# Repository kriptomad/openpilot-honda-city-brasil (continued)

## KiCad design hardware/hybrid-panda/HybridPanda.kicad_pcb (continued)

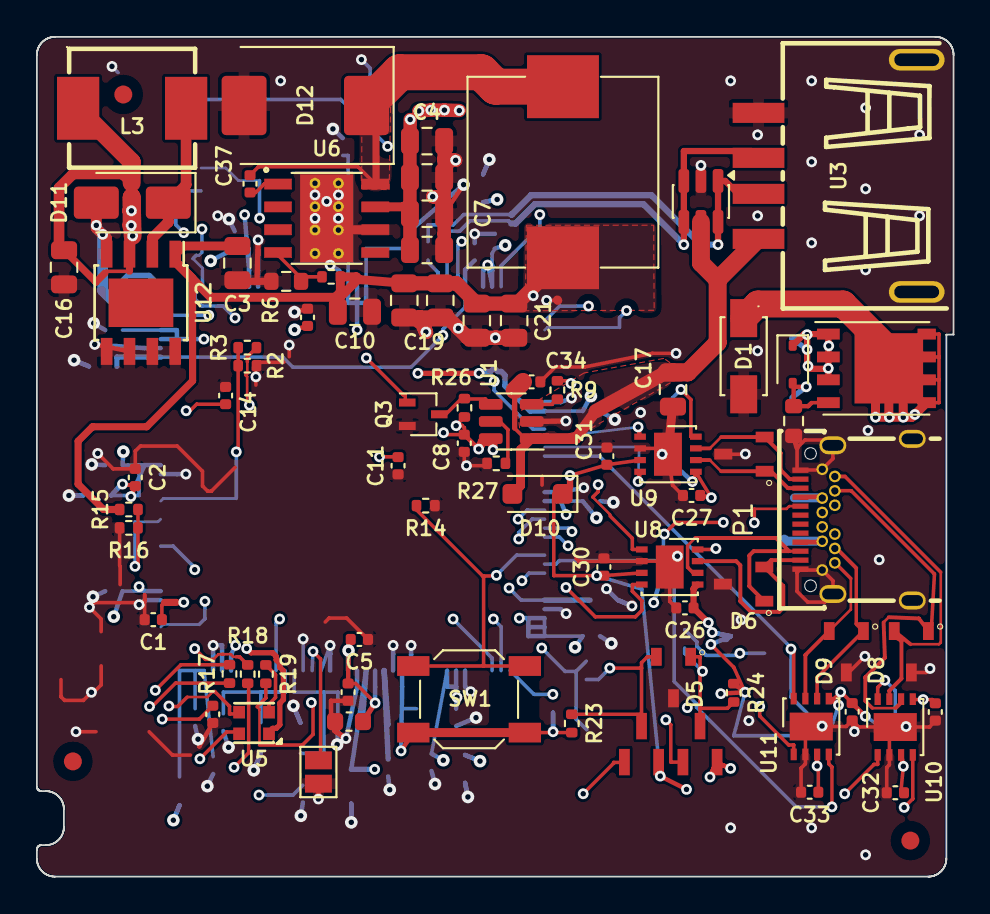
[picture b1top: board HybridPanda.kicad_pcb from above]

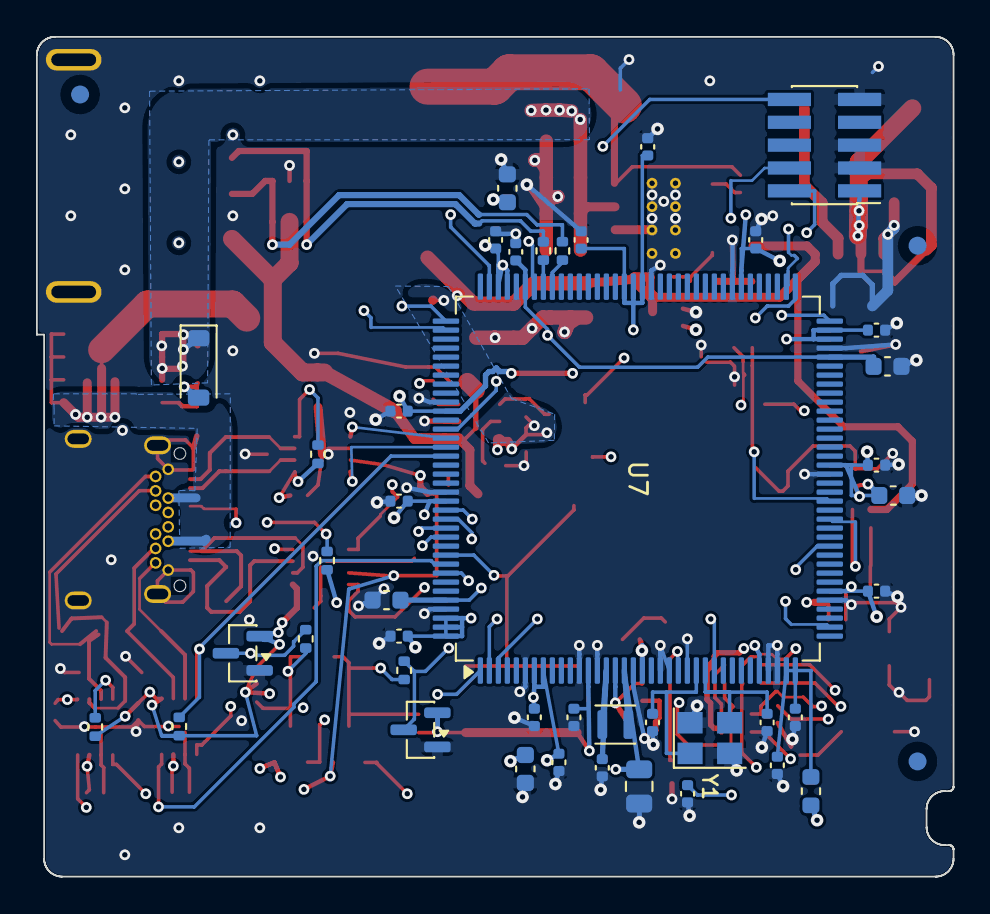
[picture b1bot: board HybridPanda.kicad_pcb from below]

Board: 4 copper layers, 50.9 x 46.7 mm, 125 parts (45 on the bottom side), 63 nets.

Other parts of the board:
FID1, FID2, FID3, FID4, FID5, FID6: Fiducial; Fiducial_1mm_Mask2mm

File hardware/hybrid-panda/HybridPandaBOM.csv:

"Id";"Designator";"Footprint";"Quantity";"Designation";"Supplier and ref";
1;"C1, C2, C5, C11, C14, C26, C27, C28, C29, C30, C31, C32, C33";"C_0402_1005Metric";13;"100NF";;;
2;"C3, C10, C16, C17, C18, C19, C20, C21";"C_0805_2012Metric";8;"47uF";;;
3;"C4, C12, C42";"C_0805_2012Metric";3;"10uF";;;
4;"C6, C7";"C_0805_2012Metric";2;"2.2uF";;;
5;"C8";"C_0402_1005Metric";1;"10uF";;;
6;"C23, C24";"C_0402_1005Metric";2;"18pF";;;
7;"C34";"C_0402_1005Metric";1;"0.1uF";;;
8;"C37";"C_0402_1005Metric";1;"10nF (LOW ESR)";;;
9;"C38, C44, C45, C46, C47, C48, C49, C50, C51, C52, C53, C54, C55, C56, C57, C58, C59";"C_0402_1005Metric";17;"100nF";;;
10;"C39, C40";"C_0603_1608Metric";2;"2.2uF";;;
11;"C41";"C_0402_1005Metric";1;"220pF";;;
12;"C43, C63";"C_0402_1005Metric";2;"1uF";;;
13;"C60, C61, C62, C65";"C_0603_1608Metric";4;"4.7uF";;;
14;"C64";"C_0402_1005Metric";1;"2.2uF";;;
15;"D1";"DIOM4325X250N";1;"SMAJ16CA-13-F";;;
16;"D2";"D_SOD-323";1;"BAS40WS 43";;;
17;"D5, D6, D7, D8, D9";"SOT95P230X110-3N";5;"PESD2CAN,215";;;
18;"D10";"D_SOD-123F";1;"BAS70H 115";;;
19;"D11";"D_SMA";1;"B320AE-13";;;
20;"D12";"D_SMC";1;"SM540C";;;
21;"D13, D14";"SOT-23";2;"BAT54S";;;
22;"D15";"D_SOD-123";1;"BZT52C12";;;
23;"FB1";"L_0603_1608Metric";1;"600R@100MHz";;;
24;"J1";"PinHeader_2x05_P1.27mm_Vertical_SMD";1;"SWD";;;
25;"L3";"IND-SMD_L7.3-W6.8";1;"47uH 2A - SMMS0650-470M";;;
26;"L4";"L_10.5x11.5_H4.0";1;"15uH";;;
27;"L5";"L_Murata_DFE201610P";1;"2.2uH DFE201610E-2R2M";;;
28;"P1";"USB-C-SMD_TYPE-C-USB-20";1;"TYPE-C-31-M-04";;;
29;"Q1, Q2";"SOT23-3";2;"DDTA143ECA-7-F P08";;;
30;"Q3";"SOT-323_SC-70";1;"PDTC114EU";;;
31;"Q4";"PowerPAK_SO-8_Single";1;"HY12P03C2";;;
32;"R1";"R_0603_1608Metric";1;"10k";;;
33;"R2";"R_0402_1005Metric";1;"1K";;;
34;"R3, R9, R23, R24, R26";"R_0402_1005Metric";5;"10K";;;
35;"R5";"R_0402_1005Metric";1;"10K (1%)";;;
36;"R6";"R_0603_1608Metric";1;"3.16K (1%)";;;
37;"R14, R15, R16, R28, R29, R30, R31, R32, R33";"R_0402_1005Metric";9;"10k";;;
38;"R17";"R_0402_1005Metric";1;"180R";;;
39;"R18";"R_0402_1005Metric";1;"110R";;;
40;"R19";"R_0402_1005Metric";1;"100R";;;
41;"R20, R21";"R_0402_1005Metric";2;"22R";;;
42;"R27";"R_0402_1005Metric";1;"2.4K";;;
43;"SW1";"SW_SPST_SKQG_WithStem";1;"SW_Push";;;
44;"U1";"SOT-23-6";1;"AP22615AWU-7";;;
45;"U3";"USB-A-TH_10.0QHHTZB6.3";1;"10_0_QHHTZB6_3";;;
46;"U5";"LED-ARRAY-SMD_4P-L2.2-W2.1-BR";1;"FM-B1921RGBA-SH";;;
47;"U6";"CONV_TPS5450DDAR";1;"TPS5450DDAR";;;
48;"U7";"LQFP-144_20x20mm_P0.5mm";1;"STM32H725ZGT6";;;
49;"U8, U9, U10, U11";"DFN-8-1EP_3x3mm_P0.65mm_EP1.55x2.4mm";4;"TJA1042TK-3";;;
50;"U12";"Diodes_PSOP-8";1;"XL1509-3.3";;;
51;"U13";"SOT-23-6";1;"USBLC6-2SC6";;;
52;"Y1";"Crystal_SMD_3225-4Pin_3.2x2.5mm";1;"25MHz X322525MOB4SI";;;

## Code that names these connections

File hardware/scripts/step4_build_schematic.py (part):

"""step4_build_schematic.py - STEP 4: rebuild hardware/hybrid-panda/HybridPanda.kicad_sch around the STM32H725ZGT6.

What it does (deterministic, re-runnable from the baseline copy made by step4_copy_and_roundtrip.py):
  1. deletes the F413 block (U7 + HSE/BOOT/VCAP/LED resistors/labels), the 5V-sense divider and the GPS block
  2. renames CANx_* labels to the firmware bus naming (BUS0/BUS1N/BUS1O/BUS2, EN->STB)
  3. enlarges the sheet to A1 and places the H725 (unit 1) with stubs, global labels, power rails and no-connects
  4. adds support blocks: HSE 25 MHz, BOOT0, NRST, SWD header, VCAP, SMPS inductor, VDDA filter, LED resistors,
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# ----------------------------------------------------------------------------- MCU pin plan (port -> net label)
# labels are global labels; shape per KiCad semantics
MCU_LABELS: dict[str, tuple[str, str]] = {
    "PB9": ("BUS0_TX", "bidirectional"), "PB8": ("BUS0_RX", "bidirectional"), "PG11": ("BUS0_STB", "bidirectional"),
    "PB6": ("BUS1N_TX", "bidirectional"), "PB5": ("BUS1N_RX", "bidirectional"), "PB3": ("BUS1N_STB", "bidirectional"),
    "PB13": ("BUS1O_TX", "bidirectional"), "PB12": ("BUS1O_RX", "bidirectional"), "PB4": ("BUS1O_STB", "bidirectional"),
    "PG9": ("BUS2_TX", "bidirectional"), "PG10": ("BUS2_RX", "bidirectional"), "PD7": ("BUS2_STB", "bidirectional"),
    "PA11": ("USB_D-", "bidirectional"), "PA12": ("USB_D+", "bidirectional"),
    "PB14": ("USB_LOAD", "output"),
    "PF11": ("VoltageSens", "input"),
    "PC4": ("SBU1_ADC", "input"), "PA1": ("SBU2_ADC", "input"),
    "PC10": ("relay_SBU1", "output"), "PC11": ("relay_SBU2", "output"),
    "PE4": ("LED_RED", "output"), "PE3": ("LED_GREEN", "output"), "PE2": ("LED_BLUE", "output"),
    "PB1": ("5VOUT_S", "input"),
    "PH0": ("HSE_IN", "passive"), "PH1": ("HSE_OUT", "passive"),
    "PA13": ("SWDIO", "bidirectional"), "PA14": ("SWCLK", "input"),
    # pin-name keys for non-port pins
    "BOOT0": ("BOOT0", "passive"), "NRST": ("NRST", "passive"),
    "VLXSMPS": ("VLXSMPS", "passive"), "VFBSMPS": ("VFBSMPS", "passive"), "VREF+": ("VDDA", "passive"),
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}
MCU_TO_3V3 = {"PDR_ON"}
# hw-type straps: board.h detects with internal pull-up, RED = all four read low -> hard-wired to GND
MCU_TO_GND = {"PF7", "PF8", "PF9", "PF10"}

# deletion regions (x0, x1, y0, y1)
REGIONS = [(258, 382, 228, 326), (238, 258, 255, 282), (105, 200, 265, 350)]
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            bottom.append(ax)
            used[f"{p.name}#{p.number}"] = "GND"
    ytop = MY - 93.98
    # HW_ID straps: join the four stub ends vertically and put one GND above the highest (below is PF11/VoltageSens)
    gnd_pts.sort(key=lambda t: t[1])
    gx = gnd_pts[0][0]
    assert all(x == gx for x, _ in gnd_pts), gnd_pts
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                  datasheet=bom["hse"].get("crystal_ds", "~"))
    pp = b.pins_abs(y1)
    b.wire(*pp["4"], 800.10, 185.42); b.pwr("GND", 800.10, 185.42, 180)
    b.wire(*pp["1"], 792.48, 190.50); b.wire(792.48, 190.50, L, 190.50); b.label("HSE_IN", L, 190.50, 180, "passive")
    b.wire(*pp["3"], 807.72, 190.50); b.wire(807.72, 190.50, 812.80, 190.50); b.label("HSE_OUT", 812.80, 190.50, 0, "passive")
    c23 = b.cap(bom["hse"]["cl_value"], 792.48, 195.58, ref="C23"); c24 = b.cap(bom["hse"]["cl_value"], 807.72, 195.58, ref="C24")
    for c, x in ((c23, 792.48), (c24, 807.72)):
        cp = b.pins_abs(c)
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
    # --- VCAP 2x2.2uF
    b.text("VCAP", 790.0, 286.0)
    b.wire(L, 292.10, 800.10, 292.10); b.label("VCAP", L, 292.10, 180, "passive")
    for x in (792.48, 800.10):
        c = b.cap("2.2uF", x, 297.18, fp="Capacitor_SMD:C_0603_1608Metric"); cp = b.pins_abs(c)
        b.wire(x, 292.10, *cp["1"]); b.wire(*cp["2"], x, 302.26); b.pwr("GND", x, 302.26)
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
    # --- SMPS: VLXSMPS -> L 2.2uH -> VFBSMPS, 220pF at VLX, 10uF at VFB, PWR_FLAG on VLXSMPS
    b.text("SMPS step-down", 790.0, 309.0)
    b.wire(L, 314.96, 795.02, 314.96); b.label("VLXSMPS", L, 314.96, 180, "passive")
    b.wire(795.02, 314.96, 800.10, 314.96); b.junction(795.02, 314.96); b.flag(795.02, 314.96)
    ind = b.symbol("Device", "L", "L", bom["smps"]["l_value"], bom["smps"]["l_fp"], 803.91, 314.96, 90, datasheet=bom["smps"].get("l_ds", "~"))
    lp = b.pins_abs(ind)
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        b.wire(x, 337.82, *cp["1"]); b.junction(x, 337.82); b.wire(*cp["2"], x, 347.98); b.pwr("GND", x, 347.98)

    # --- LED series resistors (reuse R17/R18/R19 values from baseline: 180R blue, 110R green, 100R red)
    b.text("LED drivers (PE4/PE3/PE2, active low)", 790.0, 351.0)
    for y, ref, val, net_in, net_out in ((355.60, "R19", "100R", "LED_RED", "RED-"),
                                          (360.68, "R18", "110R", "LED_GREEN", "GREEN-"),
                                          (365.76, "R17", "180R", "LED_BLUE", "BLUE-")):
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        b.wire(*dp["2"], dp["2"][0], y + 7.62); b.pwr("+3.3V", dp["2"][0], y + 7.62, 180)  # K -> 3V3
        b.wire(*dp["1"], dp["1"][0], y + 7.62); b.pwr("GND", dp["1"][0], y + 7.62, 0)      # A -> GND

    # --- 5VOUT_S divider (R15/R16 10k, +5V -> PB1)
    b.text("5V sense (PB1)", 790.0, 414.0)
    b.pwr("+5V", 792.48, 419.10)
    r15 = b.res("10k", 792.48, 424.18, ref="R15"); rp = b.pins_abs(r15)
    b.wire(792.48, 419.10, *rp["1"]); b.wire(*rp["2"], L, 426.72); b.label("5VOUT_S", L, 426.72, 180, "input")
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
def phase_project():
    """project file: name + ERC pin-conflict map (power_out<->power_out = warning, needed because the KiCad H7 symbol
    declares the three VCAP pins as power_out while ST requires them tied together; D-19)."""
    pro = PROJ / "HybridPanda.kicad_pro"
    d = json.loads(pro.read_text(encoding="utf-8"))
    d["meta"]["filename"] = "HybridPanda.kicad_pro"
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
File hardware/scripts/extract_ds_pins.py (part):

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
# (port pin, firmware source, function required, net name in new schematic)
REQUIRED = [
    ("PA11", "stm32h7/peripherals.h", "OTG_HS_DM AF10 (USB FS PHY interno; DS nomeia OTG_HS)", "USB_DM"),
    ("PA12", "stm32h7/peripherals.h", "OTG_HS_DP AF10", "USB_DP"),
    ("PF11", "stm32h7/peripherals.h", "ADC1_INP2 ADC1 ch2 (VOLT_S)", "VOLT_S"),
    ("PB8",  "stm32h7/peripherals.h", "FDCAN1_RX AF9", "FDCAN1_RX"),
    ("PB9",  "stm32h7/peripherals.h", "FDCAN1_TX AF9", "FDCAN1_TX"),
    ("PB12", "stm32h7/peripherals.h", "FDCAN2_RX AF9 (normal)", "FDCAN2_RX"),
    ("PB13", "stm32h7/peripherals.h", "FDCAN2_TX AF9 (normal)", "FDCAN2_TX"),
    ("PB5",  "stm32h7/peripherals.h", "FDCAN2_RX AF9 (OBD)", "FDCAN2OBD_RX"),
    ("PB6",  "stm32h7/peripherals.h", "FDCAN2_TX AF9 (OBD)", "FDCAN2OBD_TX"),
    ("PG9",  "stm32h7/peripherals.h", "FDCAN3_TX AF2 (firmware só define AF2; direção pelo DS)", "FDCAN3_TX"),
    ("PG10", "stm32h7/peripherals.h", "FDCAN3_RX AF2", "FDCAN3_RX"),
    ("PG11", "boards/red.h", "GPIO out: CAN0 transceiver STB (bus0)", "CAN0_STB"),
    ("PB3",  "boards/red.h", "GPIO out: OBD transceiver STB", "CAN_OBD_STB"),
    ("PD7",  "boards/red.h", "GPIO out: CAN2 transceiver STB (bus2)", "CAN2_STB"),
    ("PB4",  "boards/red.h", "GPIO out: CAN1 transceiver STB (bus1)", "CAN1_STB"),
    ("PB1",  "boards/red.h", "ADC12_INP5 analog (5VOUT_S; red.h só MODE_ANALOG)", "5VOUT_S"),
    ("PB14", "boards/red.h", "GPIO OD pull-up: USB_LOAD_EN", "USB_LOAD_EN"),
    ("PC4",  "boards/red.h", "ADC12_INP4 ADC1 ch4 (SBU1)", "SBU1"),
    ("PA1",  "boards/red.h", "ADC1_INP17 ADC1 ch17 (SBU2)", "SBU2"),
    ("PC10", "boards/red.h", "GPIO out active-low: relay SBU1", "RELAY_SBU1"),
    ("PC11", "boards/red.h", "GPIO out active-low: relay SBU2", "RELAY_SBU2"),
    ("PE4",  "boards/red.h", "GPIO OD: LED red", "LED_R"),
    ("PE3",  "boards/red.h", "GPIO OD: LED green", "LED_G"),
    ("PE2",  "boards/red.h", "GPIO OD: LED blue", "LED_B"),
    ("PF7",  "stm32h7/board.h", "GPIO in pull-up: HW_TYPE id1 bit0 (RED=0)", "HWID1_0"),
    ("PF8",  "stm32h7/board.h", "GPIO in: HW_TYPE id1 bit1 (RED=0)", "HWID1_1"),
    ("PF9",  "stm32h7/board.h", "GPIO in: HW_TYPE id1 bit2 (RED=0)", "HWID1_2"),
    ("PF10", "stm32h7/board.h", "GPIO in: HW_TYPE id1 bit3 (RED=0)", "HWID1_3"),
    ("PD4",  "stm32h7/board.h", "GPIO in pull-up: HW_TYPE id2 bit0 (PD4..PD6 != 0b011)", "HWID2_0"),
    ("PD5",  "stm32h7/board.h", "GPIO in: HW_TYPE id2 bit1", "HWID2_1"),
    ("PD6",  "stm32h7/board.h", "GPIO in: HW_TYPE id2 bit2", "HWID2_2"),
    ("PH0",  "stm32h7/clock.h", "OSC_IN (HSE 25 MHz) pino PH0-OSC_IN", "HSE_IN"),
    ("PH1",  "stm32h7/clock.h", "OSC_OUT (HSE 25 MHz) pino PH1-OSC_OUT", "HSE_OUT"),
    ("PA13", "-", "SWDIO (debug)", "SWDIO"),
    ("PA14", "-", "SWCLK (debug)", "SWCLK"),
    ("PE11", "boards/red.h (has_spi=false)", "GPIO (SPI4_NSS) unused", "NC"),
    ("PE12", "boards/red.h", "GPIO (SPI4_SCK) unused", "NC"),
    ("PE13", "boards/red.h", "GPIO (SPI4_MISO) unused", "NC"),
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row_re = re.compile(r"^(\S+) (\S+) (\S+) (\S+) (\S+) (\S+) (\S+) (\S+) (P[A-K]\d{1,2}(?:_C)?(?:-OSC_IN|-OSC_OUT|\([^)]*\)?)?|BOOT0|NRST|PDR_ON|VCAP|VDDLDO|VDDSMPS|VLXSMPS|VFBSMPS|VSSSMPS|VDD33USB|VDD50USB|VREF\+|VDDA|VSSA|VBAT|VDD|VSS)\s*(I/O|S|RST|I|O|B)?\b(.*)$", re.M)
TABLE8_START = text.find("Table 8. STM32H725 pin and ball descriptions \n")
TABLE8_END = text.find("Table 9. STM32H725 pin alternate functions \n", TABLE8_START)
# rows where the pin name wrapped onto the next line (e.g. "58 89 B6 130 H7 F7 A6 162" / "PB3(JTDO/")
row_wrap_re = re.compile(r"^(\S+) (\S+) (\S+) (\S+) (\S+) (\S+) (\S+) (\S+)$")

lines = text[TABLE8_START:TABLE8_END].splitlines()
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
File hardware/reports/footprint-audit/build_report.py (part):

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    "https://assets.nexperia.com/documents/data-sheet/BAS70H.pdf (403)",
    "Nexperia SOD123F recomendado: 2 pads ~1.1 x 1.2, span externo ~3.9 (valor de referencia; datasheet nao obtido). " + IPC,
    "2 pads 1.10 x 1.10 mm, centros +-1.40 mm (span externo 3.9) = KiCad D_SOD-123F. Marca de catodo (silk fechado) no lado do pad 1 = +5V (K); pad 2 = USB_PWR (A).",
    pin1="Catodo em +5V, anodo em USB_PWR: coerente (USB alimenta o rail 5V).")
add(("Diode_SMD", "D_SMA"), "UNVERIFIABLE", "B320AE-13 (Diodes, SMA/DO-214AC)",
    "https://www.diodes.com/assets/Datasheets/ds13006.pdf (nao baixado)",
    "Diodes SMA suggested pad (tipico): pads ~2.0-2.5 x 1.5-1.8, span externo ~6.5. " + IPC,
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    "https://assets.nexperia.com/documents/data-sheet/BAT54_SER.pdf (403)",
    "Nexperia SOT23 recomendado (tipico): pads ~1.0-1.4 x 0.6, pitch 0.95, span ~2.3-2.9. " + IPC,
    "3 pads 1.475 x 0.60 mm em x=+-0.9375, y=+-0.95 (= KiCad SOT-23). B.Cu.",
    pin1="BAT54S: 1=A1, 2=K2, 3=K1/A2 (center tap). Placa: 1=GND, 2=+3V3, 3=SBU1_ADC/SBU2 -> clamp GND..3V3 no sinal: coerente.")
add(("Diode_SMD", "D_SOD-323"), "UNVERIFIABLE", "BAS40WS,43 (Nexperia SOD323)",
    "https://assets.nexperia.com/documents/data-sheet/BAS40WS.pdf (403)",
    "Nexperia SOD323 recomendado (tipico): pads ~0.6 x 0.7, span externo ~2.7. " + IPC,
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    "Nexperia SOT23 (tipico): pads ~1.0 x 0.6, pitch 0.95, span externo ~2.9-3.3. " + IPC + " KiCad SOT-23: 1.475 x 0.6 em +-0.9375.",
    "3 pads 1.00 x 0.60 mm em x=+-1.15, y=+-0.95 (span externo 3.3, interno 1.3). Atributo THT com pads SMD (DRC). D8/D9 sem modelo 3D; D5-D7 com modelo.",
    fix="Atributo -> SMD. Atribuir modelo 3D ${KICAD10_3DMODEL_DIR}/Package_TO_SOT_SMD.3dshapes/SOT-23.step a D8/D9. Pads curtos (1.0): opcional alongar para 1.2 mantendo span externo.",
    pin1="PESD2CAN: 1=I/O1, 2=I/O2, 3=GND. Placa D5: 1=SBU1, 2=SBU2, 3=GND -> OK; D6-D9 nos pares CANH/CANL.")
add(("Connector_PinHeader_1.27mm", "PinHeader_2x05_P1.27mm_Vertical_SMD"), "OK", "header SWD 2x5 1.27 mm SMD (generico)", "-",
    "Header 1.27 mm SMD generico (ex. Samtec FTSH-105-01-L-DV): pads ~0.74 x 2.4, pitch 1.27, linhas +-1.95 (span 3.9).",
    "10 pads 2.40 x 0.74 mm, pitch 1.27, linhas em y=+-1.95 (= KiCad lib).",
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    "SOT-23 (Diodes 'Suggested pad layout' tipico / IPC): pitch 0.95 entre pinos 1-2 (dist. 1.90), pads ~1.0-1.5 x 0.6, centros em y +-0.95 a 1.0. KiCad SOT-23: 1.475 x 0.60 em x=+-0.9375, y=+-0.95.",
    "3 pads quadrados 0.914 x 0.914 mm em (+-0.889, -1.016) e (0, +1.001): distancia pinos 1-2 = 1.778 (datasheet 1.90, erro 0.12); pads curtos no eixo do terminal (0.91 vs 1.0-1.5). Sem courtyard. Modelo 3D OK.",
    fix="Substituir pads por geometria KiCad SOT-23: pads 1 e 2 em (+-0.95, +1.0) 0.6 x 1.475 (eixo do terminal em y), pad 3 em (0, -1.0); adicionar courtyard 3.3 x 3.0.",
    pin1="DDTA143ECA: 1=B(in), 2=E, 3=C. Placa Q1: 1=relay_SBU2 (base), 2=+5V (emissor, PNP), 3=SBU2 (coletor) -> coerente.")
add(("Package_TO_SOT_SMD", "SOT-323_SC-70"), "MISMATCH", "PDTC114EU (Nexperia SOT323 / SC-70)",
    "https://assets.nexperia.com/documents/data-sheet/PDTC114EU.pdf (403)",
    "Nexperia SOT323 recomendado (tipico): pads ~0.7-0.9 x 0.45-0.5 (eixo do terminal), pitch 0.65, span externo ~2.5-2.7. KiCad SOT-323_SC-70: pads 0.925 x 0.45 em x=+-0.8875, y=+-0.65 / 0.",
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    "https://www.diodes.com/assets/Datasheets/AP22615.pdf (404) / LCSC (reset)",
    "Diodes SOT-26 suggested pad (tipico): pads ~1.0-1.3 x 0.6, pitch 0.95, span externo ~3.2-3.6. KiCad SOT-23-6: 1.325 x 0.60 em x=+-1.1375, y=0/+-0.95.",
    "6 pads 1.325 x 0.60 mm em x=+-1.1375, y=0/+-0.95 (= KiCad lib).",
    pin1="AP22615 SOT-26: 1=OUT, 2=GND, 3=FLG, 4=EN, 5=ILIM, 6=IN. Placa: 1=USB_PWR, 2=GND, 3=FLG, 4=EN (Q3), 5=ISET, 6=+5V -> coerente.")
add(("Package_DFN_QFN", "DFN-8-1EP_3x3mm_P0.65mm_EP1.55x2.4mm"), "NOTE", "TJA1042TK/3 (NXP HVSON8, SOT782-1)",
    "https://www.nxp.com/docs/en/package-information/SOT782-1.pdf",
    "SOT782-1 footprint: Ay 3.25 (span externo), By 2.20 (interno), pad 0.30 x 0.525, P 0.65; EP land 2.45 x 1.65 (SLx x SLy); pasta EP 1.10 x 0.65 (1x1); ocupado 3.25 x 3.50.",
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    "DDA: 8 pads 1.55 x 0.60, pitch 1.27, span externo 5.4 (pads +-2.7 centro... TI: 1.55 x 0.6 em x=+-2.7); thermal pad 2.95 x 4.90 (exposto), abertura mascara 2.60 x 3.10, stencil 2.60 x 3.10 (0.125 mm), vias diam 0.20 (furo) em grade 1.3 mm.",
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    fix="Robustecer: pads 1-8 -> camadas F.Cu/F.Mask/F.Paste; EP -> F.Cu+F.Mask e pasta via pad com janela 2.6 x 3.1 (ou 4 retangulos); remover poligonos graficos de mascara/pasta. Vias 0.3 mm (TI 0.2) OK.",
    pin1="TPS5450: 1 BOOT, 2 NC, 3 NC, 4 VSENSE, 5 ENA, 6 GND, 7 VIN, 8 PH, 9 PowerPAD. Conferir redes no esquema.")
add(("Package_QFP", "LQFP-144_20x20mm_P0.5mm"), "NOTE", "STM32H725ZGT6 (ST LQFP144 20x20, pitch 0.5)",
    "https://www.st.com/resource/en/datasheet/stm32h725zg.pdf (timeout)",
    "ST 'LQFP144 recommended footprint' (tipico ST): pads 0.30 x 1.35, pitch 0.50, span externo 22.6, interno 19.9 (valores de referencia ST; PDF nao baixado).",
    "144 pads 1.475 x 0.30, pitch 0.50, centros +-10.6625 (span externo 22.8, interno 19.85) = KiCad lib. B.Cu. Pino 1 no canto com marca; pad 36 = VDDA, 144 = +3V3, 37 = PA0 coerentes com o pinout LQFP144 do H725.",
    notes="Pads 0.1 mm mais longos que ST e span externo +0.2: dentro da pratica IPC. Montado no lado B (espelhado no dump).",
    pin1="Pino 1 = PE2 (LED_BLUE no esquema) no canto do indice; 36 VDDA e 144 VDD coerentes com LQFP144 STM32H7.")
add(("Crystal", "Crystal_SMD_3225-4Pin_3.2x2.5mm"), "UNVERIFIABLE", "X322525MOB4SI 25 MHz (Yangxing 3225 4 pads)",
    "https://atta.szlcsc.com/... X322525MOB4SI (connection reset)",
    "Land pattern 3225 tipico (Yangxing/Abracon): pads 1.4 x 1.2, centros (+-1.1, +-0.85) (pitch 2.2 x 1.7). Datasheet nao baixado.",
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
